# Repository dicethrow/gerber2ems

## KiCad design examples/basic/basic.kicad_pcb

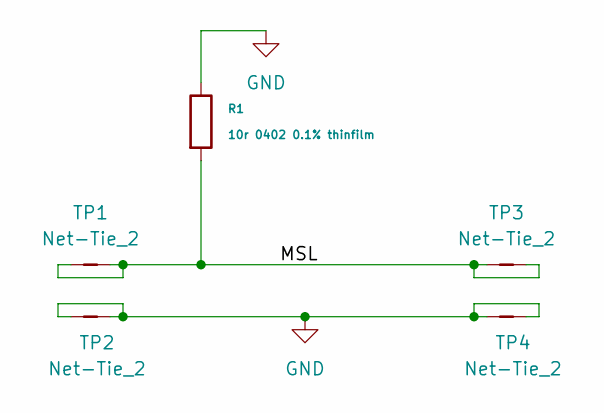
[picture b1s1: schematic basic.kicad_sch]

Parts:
R1: 10r 0402 0.1% thinfilm; R_0402_1005Metric; Mfg Part # CPF0402B10RE1
TP1, TP2, TP3, TP4: Net-Tie_2; NetTie-2_SMD_Pad0.127mm

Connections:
/MSL: R1.1, TP1.1, TP1.2, TP3.1, TP3.2
GND: R1.2, TP2.1, TP2.2, TP4.1, TP4.2

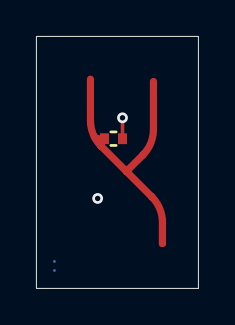
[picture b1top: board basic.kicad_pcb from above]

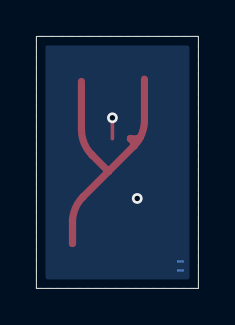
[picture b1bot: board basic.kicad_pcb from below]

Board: 2 copper layers, 9.0 x 14.0 mm, 8 parts (2 on the bottom side), 2 nets.

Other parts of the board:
SP1, SP2, SP3: Simulation_Port

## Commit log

2024-01-02 temp initial changes for testing lumped components
2024-01-02 Proof of concept mods for modeling a resistor

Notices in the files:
parts and their libraries:
License: Apache-2.0
